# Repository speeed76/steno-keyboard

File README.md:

# Steno/QWERTY dual-mode keyboard

A 42-key keyboard (3×12 + 6 thumb keys) that works as a normal QWERTY keyboard
or as a steno machine that translates chords **on the keyboard itself**, so the
computer needs no Plover install.

## Status

| Part | State |
|---|---|
| PCB (`hardware/`) | placed and netlisted, **not routed yet**. Ergogen generates `hardware/ergogen/output/pcbs/steno_qwerty.kicad_pcb`; traces still need routing in KiCad |
| Firmware (`firmware/`) | **draft, never run on hardware.** The steno engine works on a desktop against Plover's real dictionary; USB and matrix code is untested |
| Dictionary compiler (`tools/build_dictionary.py`) | works: Plover `main.json` → 2.8 MB binary file |

## Hardware constraint found so far

Plover's default dictionary is still ~2.6 MB after compiling to a compact
binary format. A standard Raspberry Pi Pico (2 MB flash, ~1 MB free under
CircuitPython) **cannot hold it**. The PCB uses the standard Pico footprint,
but fit a module with ≥4 MB of flash (Raspberry Pi Pico 2) or, better, 16 MB.

## PCB

- 42 MX switches with Kailh hotswap sockets, one diode per key (SOD-123 or THT 1N4148)
- Raspberry Pi Pico-footprint module, soldered through-hole, USB at the top edge
- MSK-12C02 slide switch at the bottom notch: GP22 to GND, closed = steno
- Matrix: rows GP6–GP9, columns GP0–GP5 (left) and GP21–GP16 (right), matching `firmware/stenokb/config.py`
- Board is ~250 × 88 mm: over JLCPCB's 100 × 100 mm budget tier, so expect ~$25–40 for 5 bare boards

Regenerate and check it:

```sh
npx ergogen@4.2.1 hardware/ergogen -o hardware/ergogen/output --clean
python3 hardware/tools/check_pcb.py hardware/ergogen/output/pcbs/steno_qwerty.kicad_pcb --png docs/pcb-preview.png
```

`check_pcb.py` is a quick placement check (single board outline, pads inside
it, no colliding switches/keycaps/Pico/switch), not a substitute for KiCad's DRC.

### Remaining steps before ordering

1. Open the `.kicad_pcb` in KiCad 8/9 and route it: by hand, with Freerouting
   (export Specctra DSN, route, import SES), or with Quilter.
2. Add GND fill zones on both layers and run DRC.
3. Plot Gerbers and drill files and upload them to JLCPCB/PCBWay.

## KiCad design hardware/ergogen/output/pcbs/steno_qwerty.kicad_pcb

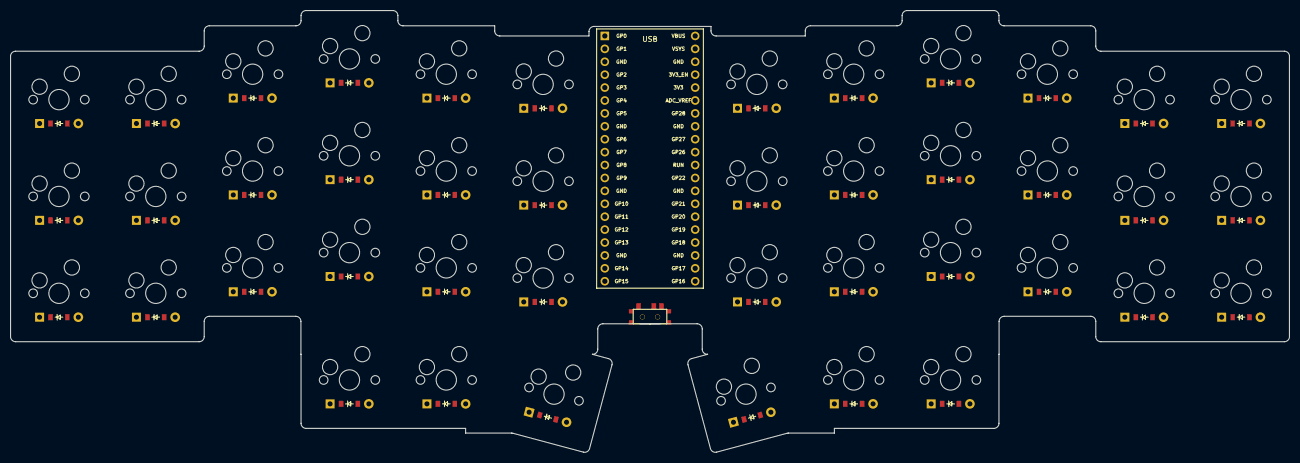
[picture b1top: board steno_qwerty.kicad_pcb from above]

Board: 2 copper layers, 251.6 x 86.9 mm, 86 parts (0 on the bottom side), 60 nets, no tracks yet.

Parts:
D1, D2, D3, D4, D5, D6, D7, D8, D9, D10, D11, D12, D13, D14, D15, D16, D17, D18, D19, D20, D21, D22, D23, D24, D25, D26, D27, D28, D29, D30, D31, D32, D33, D34, D35, D36, D37, D38, D39, D40, D41, D42: ComboDiode
MCU1: RPi Pico; RPi_Pico
S1, S2, S3, S4, S5, S6, S7, S8, S9, S10, S11, S12, S13, S14, S15, S16, S17, S18, S19, S20, S21, S22, S23, S24, S25, S26, S27, S28, S29, S30, S31, S32, S33, S34, S35, S36, S37, S38, S39, S40, S41, S42: MX
T1: SPDT_C128955

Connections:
GND: MCU1.3, MCU1.8, MCU1.13, MCU1.18, MCU1.23, MCU1.28, MCU1.33, MCU1.38, T1.2
GP0: MCU1.1, S1.1, S2.1, S3.1
GP1: MCU1.2, S4.1, S5.1, S6.1
GP2: MCU1.4, S7.1, S8.1, S9.1
GP3: MCU1.5, S10.1, S11.1, S12.1, S19.1
GP4: MCU1.6, S13.1, S14.1, S15.1, S20.1
GP5: MCU1.7, S16.1, S17.1, S18.1, S21.1
GP6: D3.1, D6.1, D9.1, D12.1, D15.1, D18.1, D24.1, D27.1, D30.1, D33.1, D36.1, D39.1, MCU1.9
GP7: D2.1, D5.1, D8.1, D11.1, D14.1, D17.1, D23.1, D26.1, D29.1, D32.1, D35.1, D38.1, MCU1.10
GP8: D1.1, D4.1, D7.1, D10.1, D13.1, D16.1, D22.1, D25.1, D28.1, D31.1, D34.1, D37.1, MCU1.11
GP9: D19.1, D20.1, D21.1, D40.1, D41.1, D42.1, MCU1.12
GP16: MCU1.21, S22.1, S23.1, S24.1
GP17: MCU1.22, S25.1, S26.1, S27.1
GP18: MCU1.24, S28.1, S29.1, S30.1
GP19: MCU1.25, S31.1, S32.1, S33.1, S40.1
GP20: MCU1.26, S34.1, S35.1, S36.1, S41.1
GP21: MCU1.27, S37.1, S38.1, S39.1, S42.1
GP22: MCU1.29, T1.1
far_cluster: D21.2, S21.2
home_cluster: D20.2, S20.2
index_bottom: D13.2, S13.2
index_home: D14.2, S14.2
index_top: D15.2, S15.2
inner_bottom: D16.2, S16.2
inner_home: D17.2, S17.2
inner_top: D18.2, S18.2
middle_bottom: D10.2, S10.2
middle_home: D11.2, S11.2
middle_top: D12.2, S12.2
mirror_far_cluster: D42.2, S42.2
mirror_home_cluster: D41.2, S41.2
mirror_index_bottom: D34.2, S34.2
mirror_index_home: D35.2, S35.2
mirror_index_top: D36.2, S36.2
mirror_inner_bottom: D37.2, S37.2
mirror_inner_home: D38.2, S38.2
mirror_inner_top: D39.2, S39.2
mirror_middle_bottom: D31.2, S31.2
mirror_middle_home: D32.2, S32.2
mirror_middle_top: D33.2, S33.2
mirror_near_cluster: D40.2, S40.2
mirror_outer_bottom: D22.2, S22.2
mirror_outer_home: D23.2, S23.2
mirror_outer_top: D24.2, S24.2
mirror_pinky_bottom: D25.2, S25.2
mirror_pinky_home: D26.2, S26.2
mirror_pinky_top: D27.2, S27.2
mirror_ring_bottom: D28.2, S28.2
mirror_ring_home: D29.2, S29.2
mirror_ring_top: D30.2, S30.2
near_cluster: D19.2, S19.2
outer_bottom: D1.2, S1.2
outer_home: D2.2, S2.2
outer_top: D3.2, S3.2
pinky_bottom: D4.2, S4.2
pinky_home: D5.2, S5.2
pinky_top: D6.2, S6.2
ring_bottom: D7.2, S7.2
ring_home: D8.2, S8.2
ring_top: D9.2, S9.2
